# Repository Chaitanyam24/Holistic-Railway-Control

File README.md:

# Holistic-Railway-Control
Arduino Based

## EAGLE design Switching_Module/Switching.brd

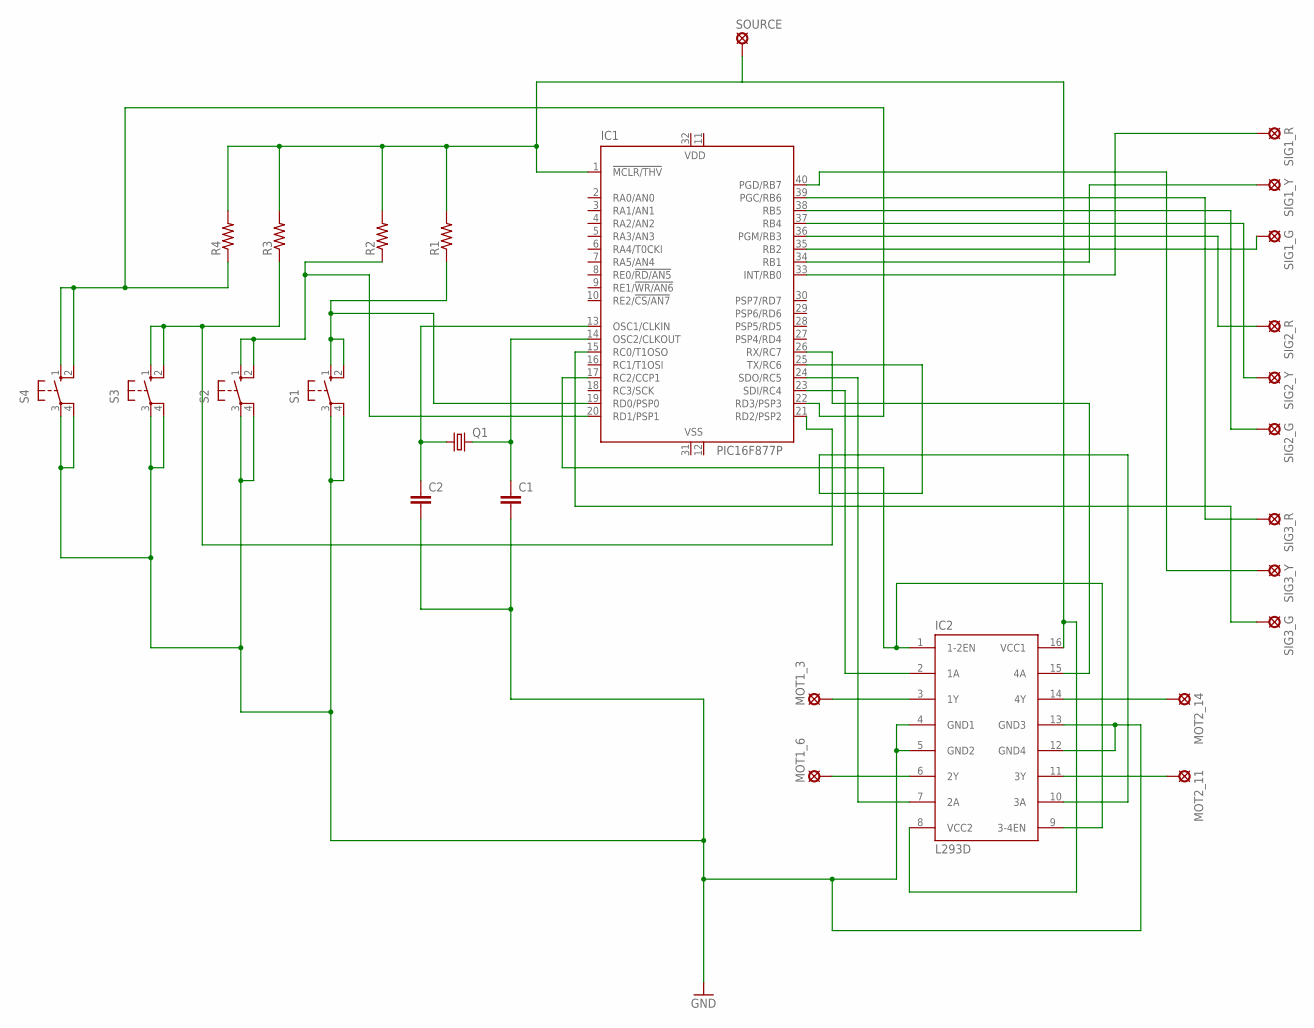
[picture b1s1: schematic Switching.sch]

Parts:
C1, C2: C-EU025-025X050; C025-025X050
IC1: PIC16F877P; DIL40
IC2: L293D; DIL16
MOT1_3, MOT1_6, MOT2_11, MOT2_14: LSP10
Q1: CRYSTALHC49U70; HC49U70
R1, R2, R3, R4: R-US_0207/10; 0207/10
S1, S2, S3, S4: 10-XX; B3F-10XX
SIG1_G, SIG1_R, SIG1_Y, SIG2_G, SIG2_R, SIG2_Y, SIG3_G, SIG3_R, SIG3_Y: LSP10
SOURCE: LSP10

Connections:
GND: C1.2, C2.2, IC2.4 (GND1), IC2.5 (GND2), IC2.12 (GND4), IC2.13 (GND3), S1.3, S1.4 (P1), S2.3, S2.4 (P1), S3.3, S3.4 (P1), S4.3, S4.4 (P1)
unnamed: IC1.33 (INT/RB0), SIG1_R.MP
unnamed: IC1.34 (RB1), SIG1_Y.MP
unnamed: IC1.35 (RB2), SIG1_G.MP
unnamed: IC1.36 (PGM/RB3), SIG2_R.MP
unnamed: IC1.37 (RB4), SIG2_Y.MP
unnamed: IC1.38 (RB5), SIG2_G.MP
unnamed: IC1.39 (PGC/RB6), SIG3_R.MP
unnamed: IC1.40 (PGD/RB7), SIG3_Y.MP
unnamed: IC1.15 (RC0/T1OSO), SIG3_G.MP
unnamed: IC1.17 (RC2/CCP1), IC2.1 (1-2EN), IC2.9 (3-4EN)
unnamed: IC1.25 (TX/RC6), IC2.10 (3A)
unnamed: IC1.26 (RX/RC7), IC2.15 (4A)
unnamed: IC1.23 (SDI/RC4), IC2.2 (1A)
unnamed: IC1.24 (SDO/RC5), IC2.7 (2A)
unnamed: IC1.1 (!MCLR/THV), IC2.8 (VCC2), IC2.16 (VCC1), R1.2, R2.2, R3.2, R4.2, SOURCE.MP
unnamed: IC2.3 (1Y), MOT1_3.MP
unnamed: IC2.6 (2Y), MOT1_6.MP
unnamed: IC2.14 (4Y), MOT2_14.MP
unnamed: IC2.11 (3Y), MOT2_11.MP
unnamed: C2.1, IC1.13 (OSC1/CLKIN), Q1.1
unnamed: C1.1, IC1.14 (OSC2/CLKOUT), Q1.2
unnamed: IC1.19 (RD0/PSP0), R1.1, S1.1 (S), S1.2 (S1)
unnamed: IC1.20 (RD1/PSP1), R2.1, S2.1 (S), S2.2 (S1)
unnamed: IC1.21 (RD2/PSP2), R3.1, S3.1 (S), S3.2 (S1)
unnamed: IC1.22 (RD3/PSP3), R4.1, S4.1 (S), S4.2 (S1)
VDD: IC1.11 (VDD), IC1.32 (VDD)
VSS: IC1.12 (VSS), IC1.31 (VSS)

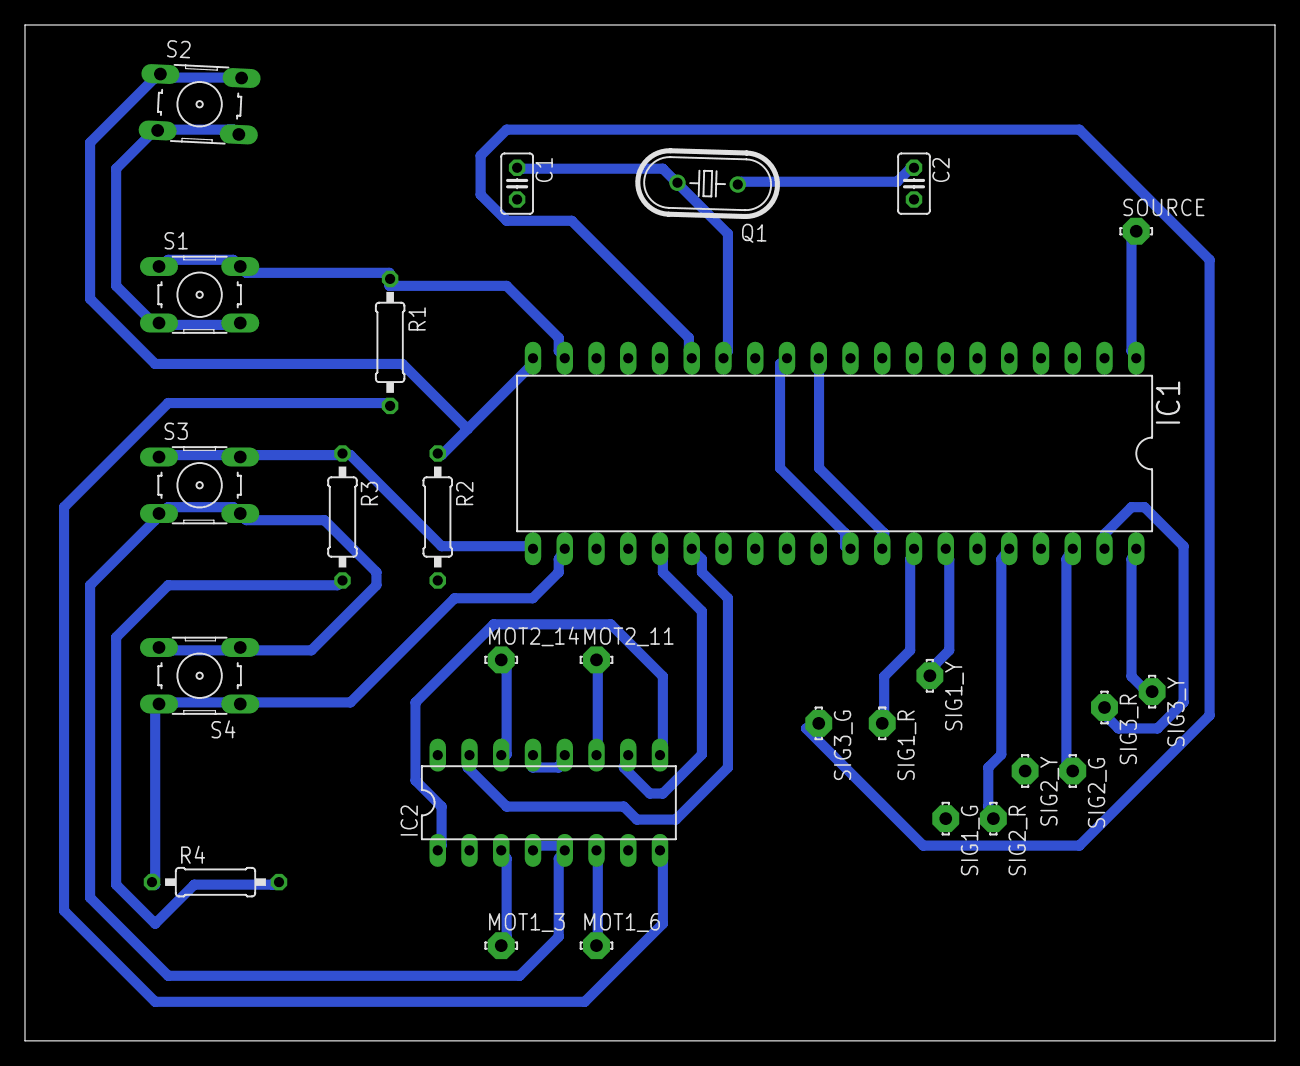
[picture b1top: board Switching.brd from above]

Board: 2 copper layers, 100.0 x 81.3 mm, 27 parts (0 on the bottom side), 28 nets.

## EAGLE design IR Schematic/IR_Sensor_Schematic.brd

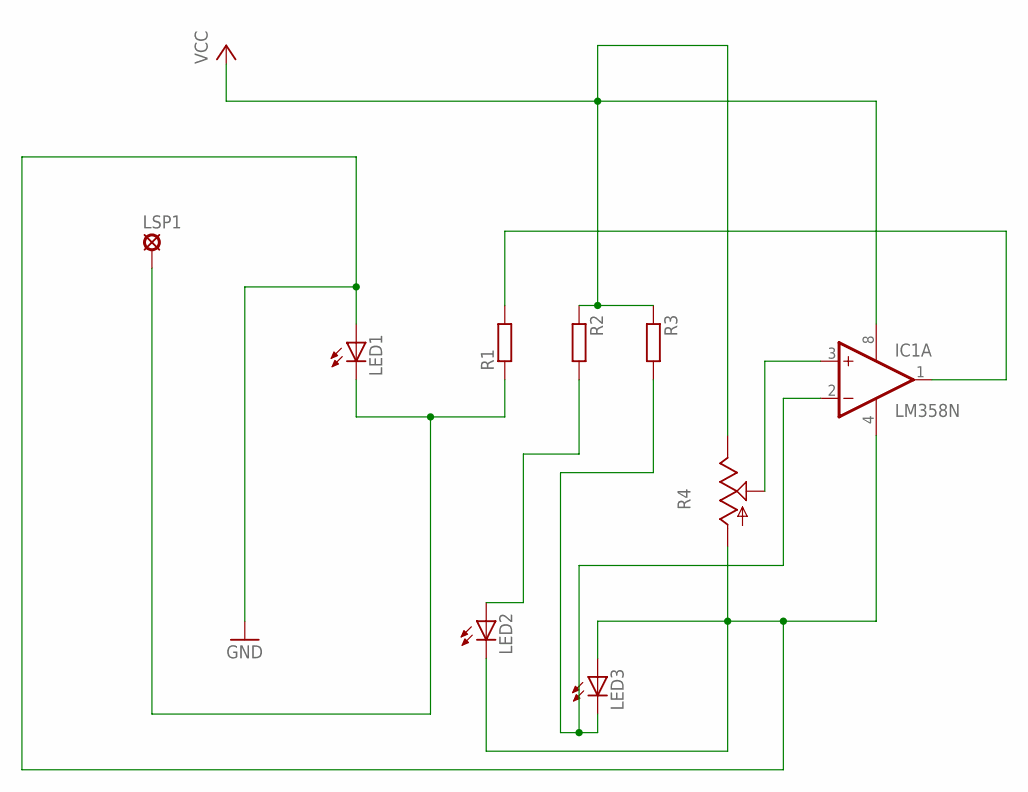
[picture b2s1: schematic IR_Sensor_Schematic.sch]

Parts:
IC1: LM358N; DIL08
LED1, LED2, LED3: LED5MM
LSP1: LSP10
R1, R2, R3: R-EU_0207_10; 0207/10
R4: TRIM_US-LI15; LI15

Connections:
GND: IC1.4 (V-), LED1.A, LED2.K (C), LED3.A, R4.A
unnamed: LED1.K (C), LSP1.MP, R1.1
unnamed: IC1.2 (-IN), LED3.K (C), R3.2
unnamed: LED2.A, R2.2
unnamed: IC1.1 (OUT), R1.2
unnamed: IC1.3 (+IN), R4.S
VCC: IC1.8 (V+), R2.1, R3.1, R4.E

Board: 2 copper layers, 9 parts (0 on the bottom side), 7 nets, no tracks yet.

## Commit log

2018-08-17 Codes
    Final
